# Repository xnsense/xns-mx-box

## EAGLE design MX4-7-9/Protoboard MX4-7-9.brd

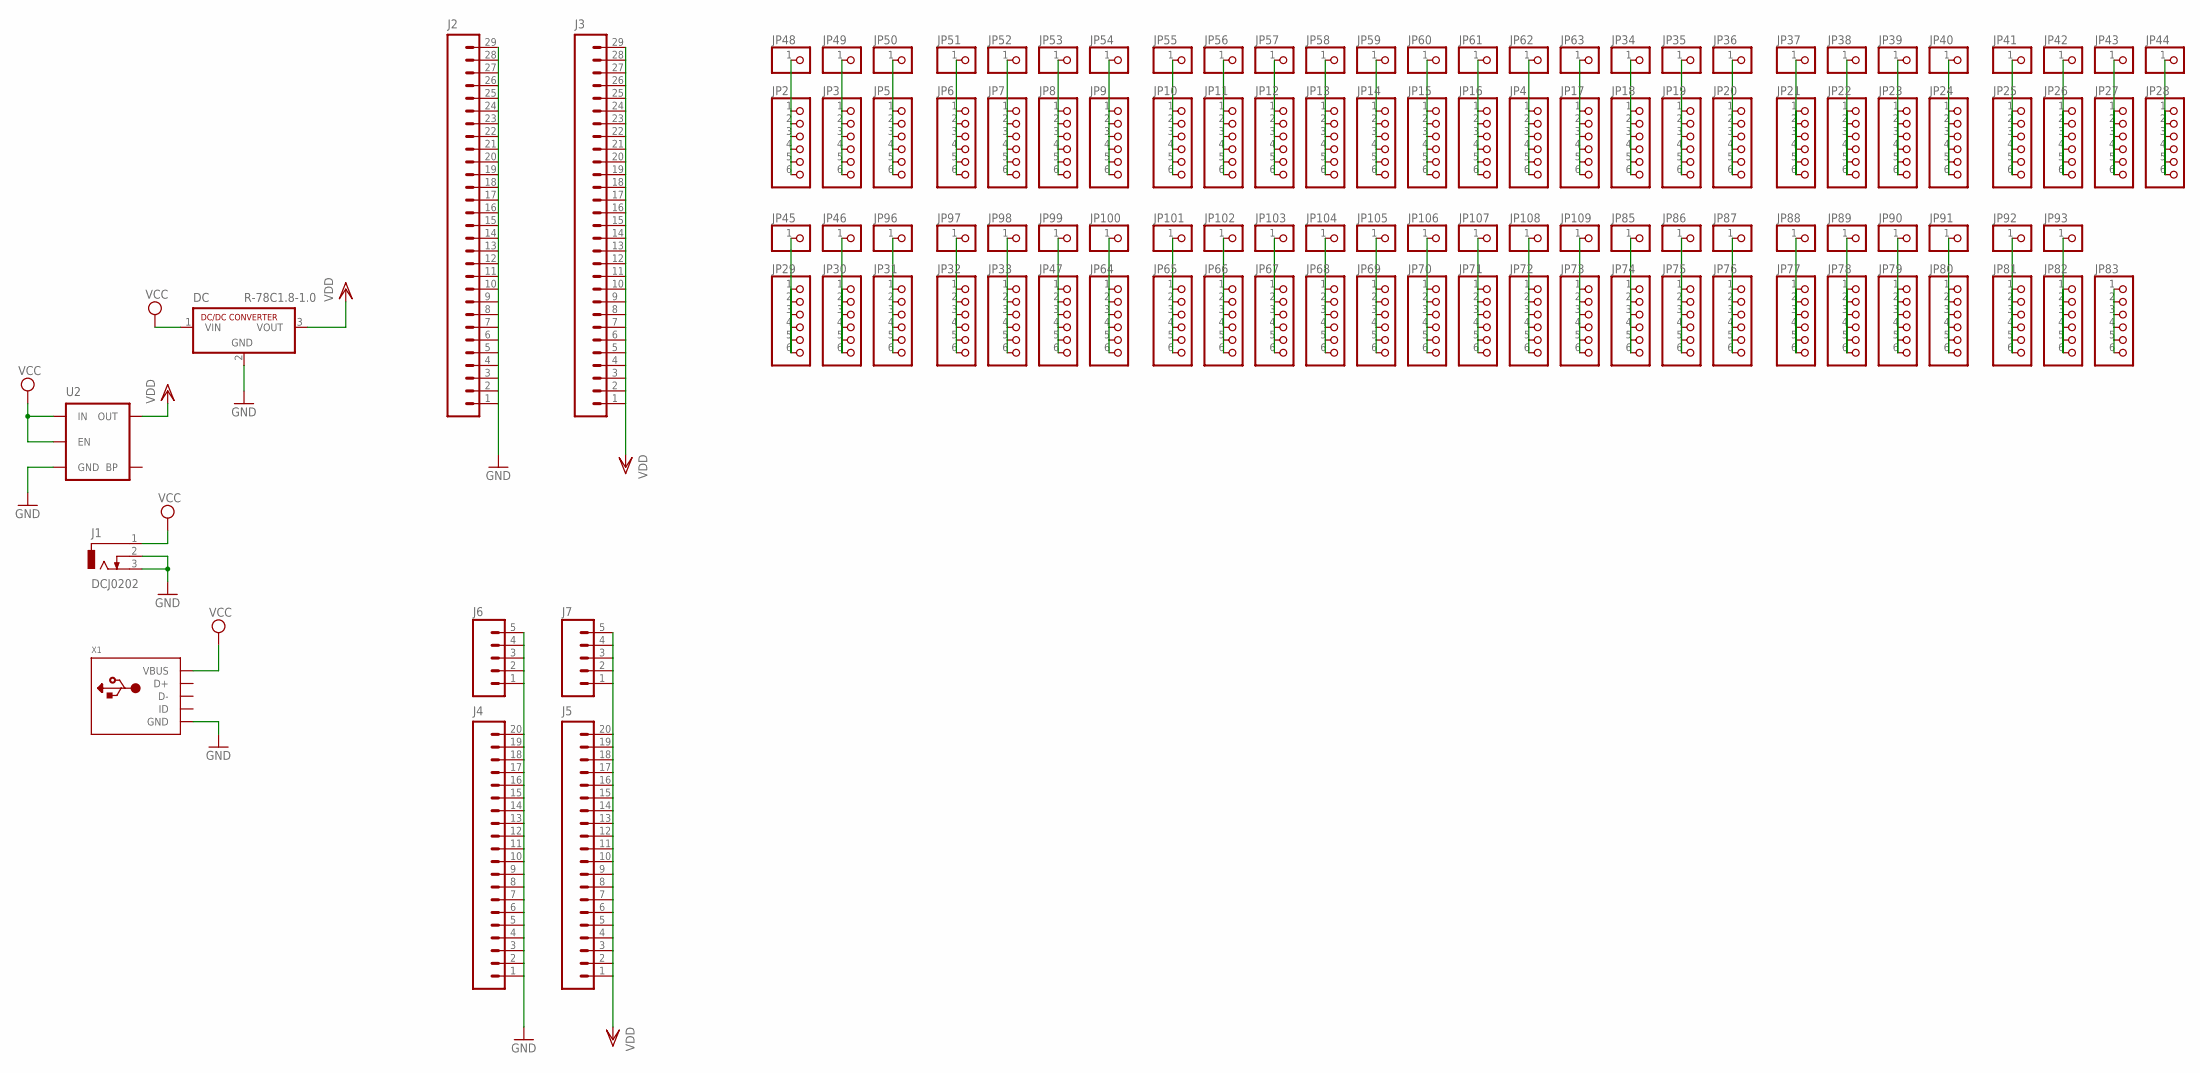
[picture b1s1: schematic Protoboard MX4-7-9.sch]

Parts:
DC: R-78C1.8-1.0; SIP3
J1: DCJ0202
J2, J3: M29NO_SILK; 1X29_NO_SILK
J4, J5: M20NO_SILK_KIT; 1X20_NO_SILK_KIT
J6, J7: M05NO_SILK; 1X05_NO_SILK
JP2, JP3, JP4, JP5, JP6, JP7, JP8, JP9, JP10, JP11, JP12, JP13, JP14, JP15, JP16, JP17, JP18, JP19, JP20, JP21, JP22, JP23, JP24, JP25, JP26, JP27, JP28, JP29, JP30, JP31, JP32, JP33, JP47, JP64, JP65, JP66, JP67, JP68, JP69, JP70, JP71, JP72, JP73, JP74, JP75, JP76, JP77, JP78, JP79, JP80, JP81, JP82, JP83: PINHD-1X6CB; 1X06-CLEANBIG
JP34, JP35, JP36, JP37, JP38, JP39, JP40, JP41, JP42, JP43, JP44, JP45, JP46, JP48, JP49, JP50, JP51, JP52, JP53, JP54, JP55, JP56, JP57, JP58, JP59, JP60, JP61, JP62, JP63, JP85, JP86, JP87, JP88, JP89, JP90, JP91, JP92, JP93, JP96, JP97, JP98, JP99, JP100, JP101, JP102, JP103, JP104, JP105, JP106, JP107, JP108, JP109: PINHD-1X1CB; 1X01-CLEANBIG
U2: MIC52053.3V; SOT23-5
X1: USBMICRO_20329; 4UCONN_20329

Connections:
GND: DC.2 (GND), J1.2, J1.3, J2.1, J2.2, J2.3, J2.4, J2.5, J2.6, J2.7, J2.8, J2.9, J2.10, J2.11, J2.12, J2.13, J2.14, J2.15, J2.16, J2.17, J2.18, J2.19, J2.20, J2.21, J2.22, J2.23, J2.24, J2.25, J2.26, J2.27, J2.28, J2.29, J4.1, J4.2, J4.3, J4.4, J4.5, J4.6, J4.7, J4.8, J4.9, J4.10, J4.11, J4.12, J4.13, J4.14, J4.15, J4.16, J4.17, J4.18, J4.19, J4.20, J6.1, J6.2, J6.3, J6.4, J6.5, U2.2 (GND), X1.BASE@1 (GND), X1.BASE@2 (GND), X1.GND, X1.SPRT@1 (GND), X1.SPRT@2 (GND), X1.SPRT@3 (GND), X1.SPRT@4 (GND)
unnamed: JP2.1, JP2.2, JP2.3, JP2.4, JP2.5, JP2.6, JP48.1
unnamed: JP31.1, JP31.2, JP31.3, JP31.4, JP31.5, JP31.6, JP96.1
unnamed: JP32.1, JP32.2, JP32.3, JP32.4, JP32.5, JP32.6, JP97.1
unnamed: JP33.1, JP33.2, JP33.3, JP33.4, JP33.5, JP33.6, JP98.1
unnamed: JP3.1, JP3.2, JP3.3, JP3.4, JP3.5, JP3.6, JP49.1
unnamed: JP5.1, JP5.2, JP5.3, JP5.4, JP5.5, JP5.6, JP50.1
unnamed: JP6.1, JP6.2, JP6.3, JP6.4, JP6.5, JP6.6, JP51.1
unnamed: JP7.1, JP7.2, JP7.3, JP7.4, JP7.5, JP7.6, JP52.1
unnamed: JP8.1, JP8.2, JP8.3, JP8.4, JP8.5, JP8.6, JP53.1
unnamed: JP9.1, JP9.2, JP9.3, JP9.4, JP9.5, JP9.6, JP54.1
unnamed: JP10.1, JP10.2, JP10.3, JP10.4, JP10.5, JP10.6, JP55.1
unnamed: JP11.1, JP11.2, JP11.3, JP11.4, JP11.5, JP11.6, JP56.1
unnamed: JP12.1, JP12.2, JP12.3, JP12.4, JP12.5, JP12.6, JP57.1
unnamed: JP13.1, JP13.2, JP13.3, JP13.4, JP13.5, JP13.6, JP58.1
unnamed: JP14.1, JP14.2, JP14.3, JP14.4, JP14.5, JP14.6, JP59.1
unnamed: JP15.1, JP15.2, JP15.3, JP15.4, JP15.5, JP15.6, JP60.1
unnamed: JP16.1, JP16.2, JP16.3, JP16.4, JP16.5, JP16.6, JP61.1
unnamed: JP4.1, JP4.2, JP4.3, JP4.4, JP4.5, JP4.6, JP62.1
unnamed: JP17.1, JP17.2, JP17.3, JP17.4, JP17.5, JP17.6, JP63.1
unnamed: JP18.1, JP18.2, JP18.3, JP18.4, JP18.5, JP18.6, JP34.1
unnamed: JP19.1, JP19.2, JP19.3, JP19.4, JP19.5, JP19.6, JP35.1
unnamed: JP20.1, JP20.2, JP20.3, JP20.4, JP20.5, JP20.6, JP36.1
unnamed: JP47.1, JP47.2, JP47.3, JP47.4, JP47.5, JP47.6, JP99.1
unnamed: JP64.1, JP64.2, JP64.3, JP64.4, JP64.5, JP64.6, JP100.1
unnamed: JP65.1, JP65.2, JP65.3, JP65.4, JP65.5, JP65.6, JP101.1
unnamed: JP21.1, JP21.2, JP21.3, JP21.4, JP21.5, JP21.6, JP37.1
unnamed: JP22.1, JP22.2, JP22.3, JP22.4, JP22.5, JP22.6, JP38.1
unnamed: JP23.1, JP23.2, JP23.3, JP23.4, JP23.5, JP23.6, JP39.1
unnamed: JP24.1, JP24.2, JP24.3, JP24.4, JP24.5, JP24.6, JP40.1
unnamed: JP25.1, JP25.2, JP25.3, JP25.4, JP25.5, JP25.6, JP41.1
unnamed: JP26.1, JP26.2, JP26.3, JP26.4, JP26.5, JP26.6, JP42.1
unnamed: JP27.1, JP27.2, JP27.3, JP27.4, JP27.5, JP27.6, JP43.1
unnamed: JP66.1, JP66.2, JP66.3, JP66.4, JP66.5, JP66.6, JP102.1
unnamed: JP28.1, JP28.2, JP28.3, JP28.4, JP28.5, JP28.6, JP44.1
unnamed: JP29.1, JP29.2, JP29.3, JP29.4, JP29.5, JP29.6, JP45.1
unnamed: JP30.1, JP30.2, JP30.3, JP30.4, JP30.5, JP30.6, JP46.1
unnamed: JP67.1, JP67.2, JP67.3, JP67.4, JP67.5, JP67.6, JP103.1
unnamed: JP68.1, JP68.2, JP68.3, JP68.4, JP68.5, JP68.6, JP104.1
unnamed: JP69.1, JP69.2, JP69.3, JP69.4, JP69.5, JP69.6, JP105.1
unnamed: JP70.1, JP70.2, JP70.3, JP70.4, JP70.5, JP70.6, JP106.1
unnamed: JP71.1, JP71.2, JP71.3, JP71.4, JP71.5, JP71.6, JP107.1
unnamed: JP72.1, JP72.2, JP72.3, JP72.4, JP72.5, JP72.6, JP108.1
unnamed: JP73.1, JP73.2, JP73.3, JP73.4, JP73.5, JP73.6, JP109.1
unnamed: JP74.1, JP74.2, JP74.3, JP74.4, JP74.5, JP74.6, JP85.1
unnamed: JP75.1, JP75.2, JP75.3, JP75.4, JP75.5, JP75.6, JP86.1
unnamed: JP76.1, JP76.2, JP76.3, JP76.4, JP76.5, JP76.6, JP87.1
unnamed: JP77.1, JP77.2, JP77.3, JP77.4, JP77.5, JP77.6, JP88.1
unnamed: JP78.1, JP78.2, JP78.3, JP78.4, JP78.5, JP78.6, JP89.1
unnamed: JP79.1, JP79.2, JP79.3, JP79.4, JP79.5, JP79.6, JP90.1
unnamed: JP80.1, JP80.2, JP80.3, JP80.4, JP80.5, JP80.6, JP91.1
unnamed: JP81.1, JP81.2, JP81.3, JP81.4, JP81.5, JP81.6, JP92.1
unnamed: JP82.1, JP82.2, JP82.3, JP82.4, JP82.5, JP82.6, JP93.1
unnamed: JP83.1, JP83.2, JP83.3, JP83.4, JP83.5, JP83.6
VCC: DC.1 (VIN), J1.1, U2.1 (IN), U2.3 (EN), X1.VBUS
VDD: DC.3 (VOUT), J3.1, J3.2, J3.3, J3.4, J3.5, J3.6, J3.7, J3.8, J3.9, J3.10, J3.11, J3.12, J3.13, J3.14, J3.15, J3.16, J3.17, J3.18, J3.19, J3.20, J3.21, J3.22, J3.23, J3.24, J3.25, J3.26, J3.27, J3.28, J3.29, J5.1, J5.2, J5.3, J5.4, J5.5, J5.6, J5.7, J5.8, J5.9, J5.10, J5.11, J5.12, J5.13, J5.14, J5.15, J5.16, J5.17, J5.18, J5.19, J5.20, J7.1, J7.2, J7.3, J7.4, J7.5, U2.5 (OUT)

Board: 2 copper layers, 115 parts (0 on the bottom side), 56 nets, no tracks yet.

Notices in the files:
parts and their libraries:
SparkFun-PowerIC: Licensing: Creative Commons ShareAlike 4.0 International - https://creativecommons.org/licenses/by-sa/4.0
